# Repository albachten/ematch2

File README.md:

# Ematch2 - testing another ematch control circuit

* Allow reading continuity w/3.3V ADC
* Allow up to 20V for firing

[Schematic pdf](v1.0.Ematch2.pdf)

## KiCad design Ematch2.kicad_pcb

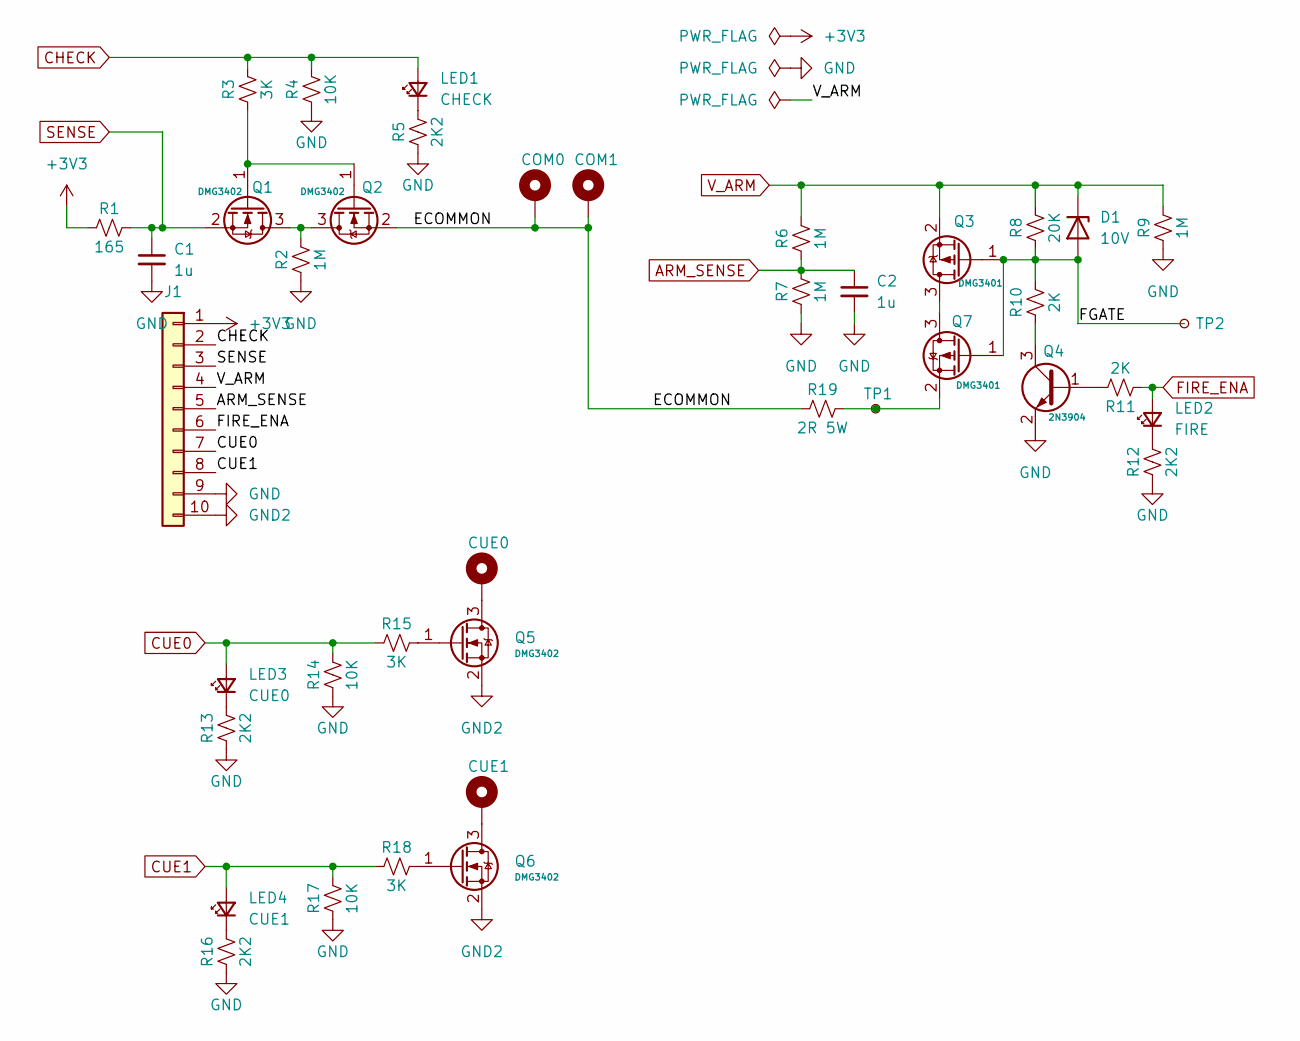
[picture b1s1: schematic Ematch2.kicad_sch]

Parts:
C1, C2: 1u; R_0805_2012Metric
CLIP1: COM0; MiniPyroClip
CLIP2: COM1; MiniPyroClip
CLIP3: CUE0; MiniPyroClip
CLIP4: CUE1; MiniPyroClip
D1: 10V; SOT-23
J1: Conn_01x10; PinHeader_1x10_P2.54mm_Vertical
LED1: CHECK; LED_0805_2012Metric
LED2: FIRE; LED_0805_2012Metric
LED3: CUE0; LED_0805_2012Metric
LED4: CUE1; LED_0805_2012Metric
Q1, Q2, Q5, Q6: DMG3402; SOT-23
Q3, Q7: DMG3401; SC-59
Q4: 2N3904; SOT-23
R1: 165; R_0805_2012Metric
R2, R6, R7, R9: 1M; R_0805_2012Metric
R3, R15, R18: 3K; R_0805_2012Metric
R4, R14, R17: 10K; R_0805_2012Metric
R5, R12, R13, R16: 2K2; R_0805_2012Metric
R8: 20K; R_0805_2012Metric
R10, R11: 2K; R_0805_2012Metric
R19: 2R 5W; R_Axial_Power_L25.0mm_W6.4mm_P27.94mm
TP1, TP2: TestPoint_Small; TestPoint_Pad_1.0x1.0mm

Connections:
+3V3: J1.1, R1.1
/ECOMMON: CLIP1.1, CLIP2.1, Q2.2 (S), R19.1
/FGATE: D1.1 (A), Q3.1 (G), Q7.1 (G), R8.1, R10.2, TP2.1
ARM_SENSE: C2.1, J1.5, R6.1, R7.2
CHECK: J1.2, LED1.2 (A), R3.2, R4.2
CUE0: J1.7, LED3.2 (A), R14.2, R15.1
CUE1: J1.8, LED4.2 (A), R17.2, R18.1
FIRE_ENA: J1.6, LED2.2 (A), R11.1
GND: C1.2, C2.2, J1.9, Q4.2 (E), R2.1, R4.1, R5.1, R7.1, R9.1, R12.1, R13.1, R14.1, R16.1, R17.1
GND2: J1.10, Q5.2 (S), Q6.2 (S)
unnamed: LED1.1 (K), R5.2
unnamed: LED2.1 (K), R12.2
unnamed: LED3.1 (K), R13.2
unnamed: LED4.1 (K), R16.2
unnamed: Q1.3 (D), Q2.3 (D), R2.2
unnamed: Q1.1 (G), Q2.1 (G), R3.1
unnamed: Q3.3 (D), Q7.3 (D)
unnamed: Q4.1 (B), R11.2
unnamed: Q4.3 (C), R10.1
unnamed: CLIP3.1, Q5.3 (D)
unnamed: Q5.1 (G), R15.2
unnamed: CLIP4.1, Q6.3 (D)
unnamed: Q6.1 (G), R18.2
unnamed: Q7.2 (S), R19.2, TP1.1
SENSE: C1.1, J1.3, Q1.2 (S), R1.2
V_ARM: D1.3 (K), J1.4, Q3.2 (S), R6.2, R8.2, R9.2

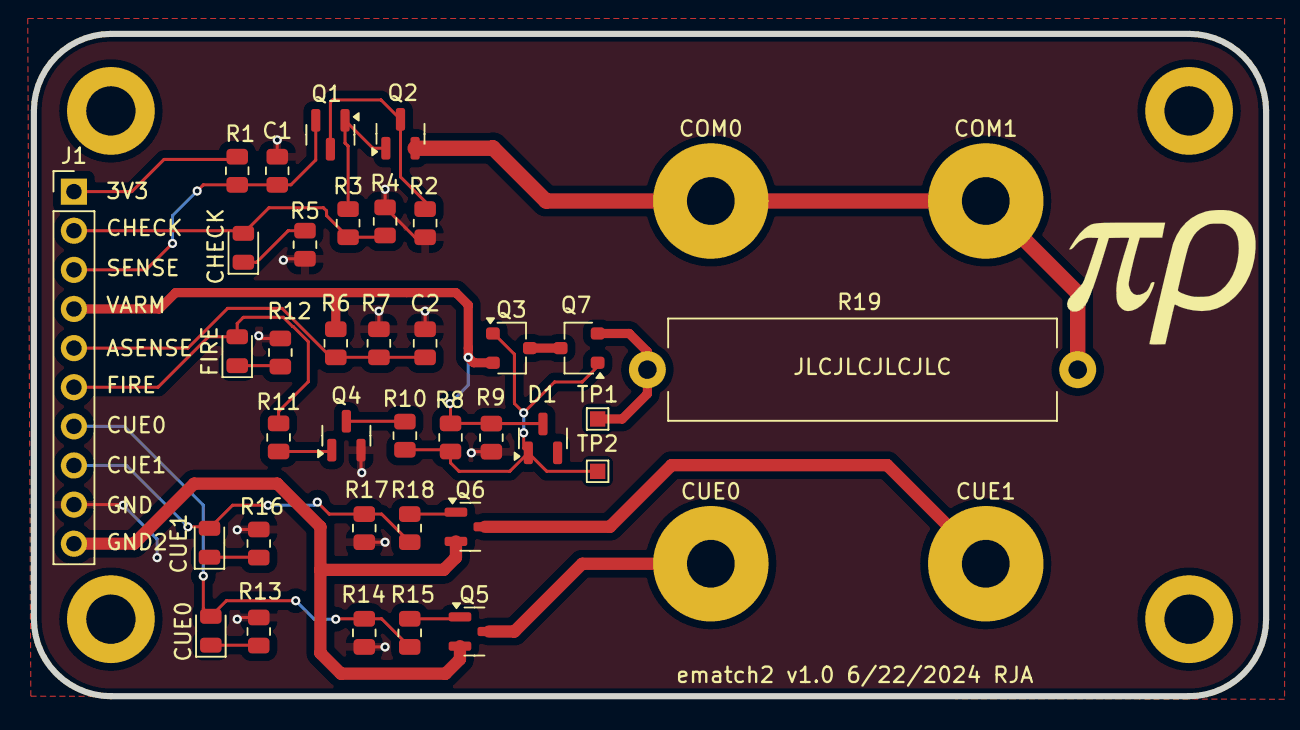
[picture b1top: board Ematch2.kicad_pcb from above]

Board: 2 copper layers, 80.0 x 43.0 mm, 40 parts (0 on the bottom side), 26 nets.

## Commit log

2024-06-23 v1.0
2024-06-23 add 3d models for pyro clips
